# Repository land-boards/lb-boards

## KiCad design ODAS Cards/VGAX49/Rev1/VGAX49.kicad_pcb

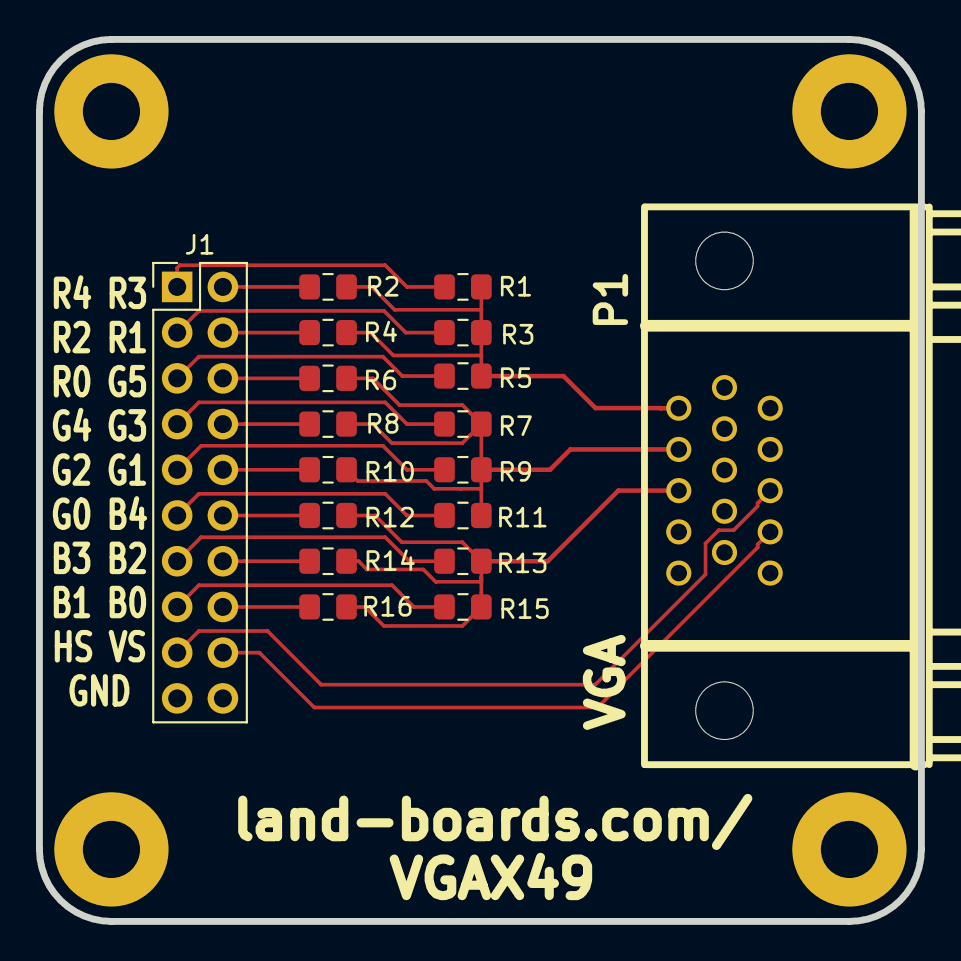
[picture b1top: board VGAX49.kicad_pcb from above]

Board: 2 copper layers, 49.0 x 49.0 mm, 22 parts (0 on the bottom side), 22 nets.

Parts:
J1: Conn_02x10_Odd_Even; PinHeader_2x10_P2.54mm_Vertical
MTG1, MTG2, MTG3, MTG4: CONN_1; MTG-4-40
P1: VGA; DB_15F-VGA-fixed
R1, R6, R12: 510; R_0805_2012Metric_Pad1.15x1.40mm_HandSolder
R2, R7, R13: 1K; R_0805_2012Metric_Pad1.15x1.40mm_HandSolder
R3, R8, R14: 2.2K; R_0805_2012Metric_Pad1.15x1.40mm_HandSolder
R4, R9, R15: 4.7K; R_0805_2012Metric_Pad1.15x1.40mm_HandSolder
R5, R10, R16: 10K; R_0805_2012Metric_Pad1.15x1.40mm_HandSolder
R11: 22K; R_0805_2012Metric_Pad1.15x1.40mm_HandSolder

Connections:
/B0: J1.16, R16.2
/B1: J1.15, R15.2
/B2: J1.14, R14.2
/B3: J1.13, R13.2
/B4: J1.12, R12.2
/G0: J1.11, R11.2
/G1: J1.10, R10.2
/G2: J1.9, R9.2
/G3: J1.8, R8.2
/G4: J1.7, R7.2
/G5: J1.6, R6.2
/HS: J1.17, P1.13
/R0: J1.5, R5.2
/R1: J1.4, R4.2
/R2: J1.3, R3.2
/R3: J1.2, R2.2
/R4: J1.1, R1.2
/VS: J1.18, P1.14
GND: J1.19, J1.20, P1.5, P1.6, P1.7, P1.8
unnamed: P1.1, R1.1, R2.1, R3.1, R4.1, R5.1
unnamed: P1.2, R6.1, R7.1, R8.1, R9.1, R10.1, R11.1
unnamed: P1.3, R12.1, R13.1, R14.1, R15.1, R16.1

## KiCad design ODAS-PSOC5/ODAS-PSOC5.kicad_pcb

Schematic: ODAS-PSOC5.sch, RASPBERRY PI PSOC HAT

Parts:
C1, C2, C3, C4, C5, C6, C9, C12, C13, C14, C15, C16: 0.1uF; C_0805_HandSoldering
C7, C10: C; C_0805_HandSoldering
C8, C11: 1uF; C_0805_HandSoldering
DS1: LED-fixed; LED_0805
F1, F2: FUSE; R_1206_HandSoldering
FID1, FID2: CONN_1; FIDUCIAL
H1: CONN_01X04; Pin_Header_Straight_1x04
H2: CONN_2; Pin_Header_Straight_2x01
H3, H4: CONN_01X03; Pin_Header_Straight_1x03
J1: DCJ0202; JACK_3.5MM
J2: USB-MICRO-B; USB_Micro-B-Wellco-SMT
MTG1, MTG2, MTG3, MTG4: CONN_1; MTG-6-32
P1: CONN_01X40; Pin_Header_Angled_2x20
P2: CONN_01X04; Pin_Header_Angled_1x04
P3: CONN_02X02; Pin_Header_Straight_2x02
P4: CONN_01X06; Pin_Header_Straight_1x06
R1: 1K; R_0805_HandSoldering
R2, R3, R4: 3.9K; R_0805_HandSoldering
R5: 120; R_0805_HandSoldering
R6, R7: 22; R_0805_HandSoldering
TEST1: COUPON; TEST_BLK-REAR
U1: 24C32; SO8E-wider
U2: CY8C5267AXI-LP051; TQFP-100_14x14mm_Pitch0.5mm
U3, U4: AP1117; SOT223
Y1: Crystal_Small; Crystal_HC49-U_Vertical

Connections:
+3.3VP: C4.1, C5.1, F1.1, H3.1, H4.1, U2.26 (VDDIO1), U2.100 (VDDIO2)
+3V3: C1.1, C15.1, C16.1, F1.2, P2.2, P4.2, R1.1, R2.2, R3.2, R4.2, U1.8 (VCC), U4.2 (VO)
+5V: C9.2, C13.1, C14.1, F2.2, U2.37 (VDDD), U2.65 (VDDA), U2.88 (VDDD), U3.2 (VO), U4.3 (VI)
+5VP: F2.1, H3.3, H4.3
/+9V: C12.1, J1.1, U3.3 (VI)
/IO_22: C2.1, H1.2, R4.1, U2.15 (~XRES)
/IO_23: H1.3, U2.21 (P1[1]/TCK/SWDCK)
/IO_24: H1.4, U2.20 (P1[0]/TMS/SWDIO)
/P5-4: R5.1, U2.31 (P5[4])
/P44: P1.34, U2.44 (P3[0])
/P45: P1.33, U2.45 (P3[1])
/P46: P1.32, U2.46 (P3[2])
/P47: P1.31, U2.47 (P3[3])
/P48: P1.30, U2.48 (P3[4])
/P49: P1.29, U2.49 (P3[5])
/P51: P1.28, U2.51 (P3[6])
/P52: P1.27, U2.52 (P3[7])
/P53: P1.26, U2.53 (I2C1_SCL/P12[0])
/P54: P1.25, U2.54 (I2C1_SDA/P12[1])
/P55: P1.24, U2.55 (P15[2])
/P56: P1.23, U2.56 (P15[3])
/P67: P1.22, U2.67 (P12[2])
/P68: P1.21, U2.68 (P12[3])
/P69: P1.20, U2.69 (P4[0])
/P70: P1.19, U2.70 (P4[1])
/P71: P1.18, U2.71 (P0[0])
/P72: P1.17, U2.72 (P0[1])
/P73: P1.16, U2.73 (P0[2])
/P74: P1.15, U2.74 (P0[3])
/P76: P1.14, U2.76 (P0[4])
/P77: P1.13, U2.77 (P0[5])
/P78: P1.12, U2.78 (P0[6])
/P79: P1.11, U2.79 (P0[7])
/P80: P1.10, U2.80 (P4[2])
/P81: P1.9, U2.81 (P4[3])
/P82: P1.8, U2.82 (P4[4])
/P83: P1.7, U2.83 (P4[5])
/P84: P1.6, U2.84 (P4[6])
/P85: P1.5, U2.85 (P4[7])
/SCL: P2.4, P3.4, U1.6 (SCL), U2.4 (I2C0_SCL/P12[4])
/SDA: P2.3, P3.2, U1.5 (SDA), U2.5 (I2C2_SDA/P12[5])
/SPICE0: P4.3, U2.6 (P6[4])
/SPIMISO: P4.5, U2.8 (P6[6])
/SPIMOSI: P4.6, U2.9 (P6[7])
/SPISCK: P4.4, U2.7 (P6[5])
/USB-DM: J2.2 (D-), R6.1
/USB-DP: J2.3 (D+), R7.1
/VZ0: C3.1, H4.2, P1.3, P1.4, U2.75 (VDDIO0)
/VZ3: C6.1, H3.2, P1.35, P1.36, U2.50 (VDDIO3)
/WR: H2.1, R1.2, U1.7 (~WP)
GND: C1.2, C2.2, C3.2, C4.2, C5.2, C6.2, C7.1, C8.1, C9.1, C10.1, C11.1, C12.2, C13.2, C14.2, C15.2, C16.2, DS1.1, H1.1, H2.2 (PM), J1.2, J1.3, J2.5 (GND), P1.1, P1.2, P1.37, P1.38, P2.1, P4.1, U1.1 (A0), U1.2 (A1), U1.3 (A2), U1.4 (GND), U2.10 (VSSB), U2.12 (VBOOST), U2.13 (VBAT), U2.14 (VSSD), U2.38 (VSSD), U2.64 (VSSA), U2.66 (VSSD), U2.87 (VSSD), U3.1 (GND/ADJ), U4.1 (GND/ADJ)
unnamed: C7.2, U2.43 (P15[1]), Y1.1
unnamed: C8.2, U2.39 (VCCD), U2.86 (VCCD)
unnamed: C10.2, U2.42 (P15[0]), Y1.2
unnamed: C11.2, U2.63 (VCCA)
unnamed: DS1.2, R5.2
unnamed: P3.1, R2.1
unnamed: P3.3, R3.1
unnamed: R6.2, U2.36 (DM/P15[7])
unnamed: R7.2, U2.35 (DP/P15[6])

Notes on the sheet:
WRITE ENABLE

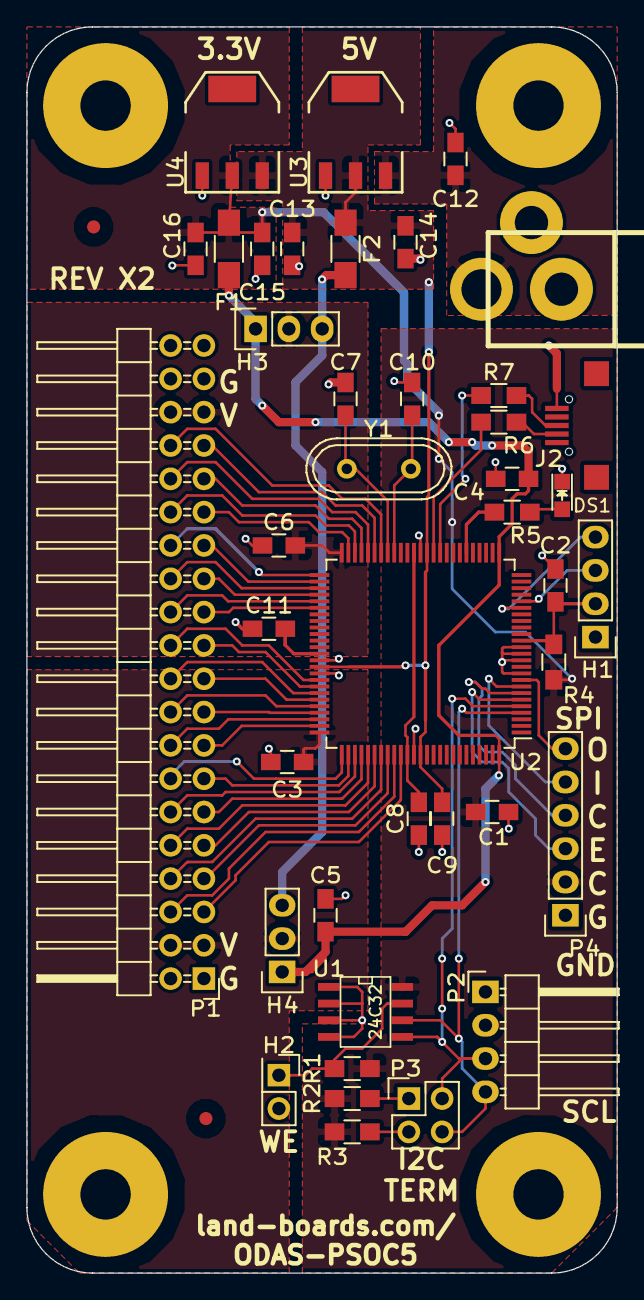
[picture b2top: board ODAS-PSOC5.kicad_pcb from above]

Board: 2 copper layers, 45.0 x 95.0 mm, 48 parts (1 on the bottom side), 60 nets.

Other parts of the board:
TEST: COUPON; REV_BLOCK

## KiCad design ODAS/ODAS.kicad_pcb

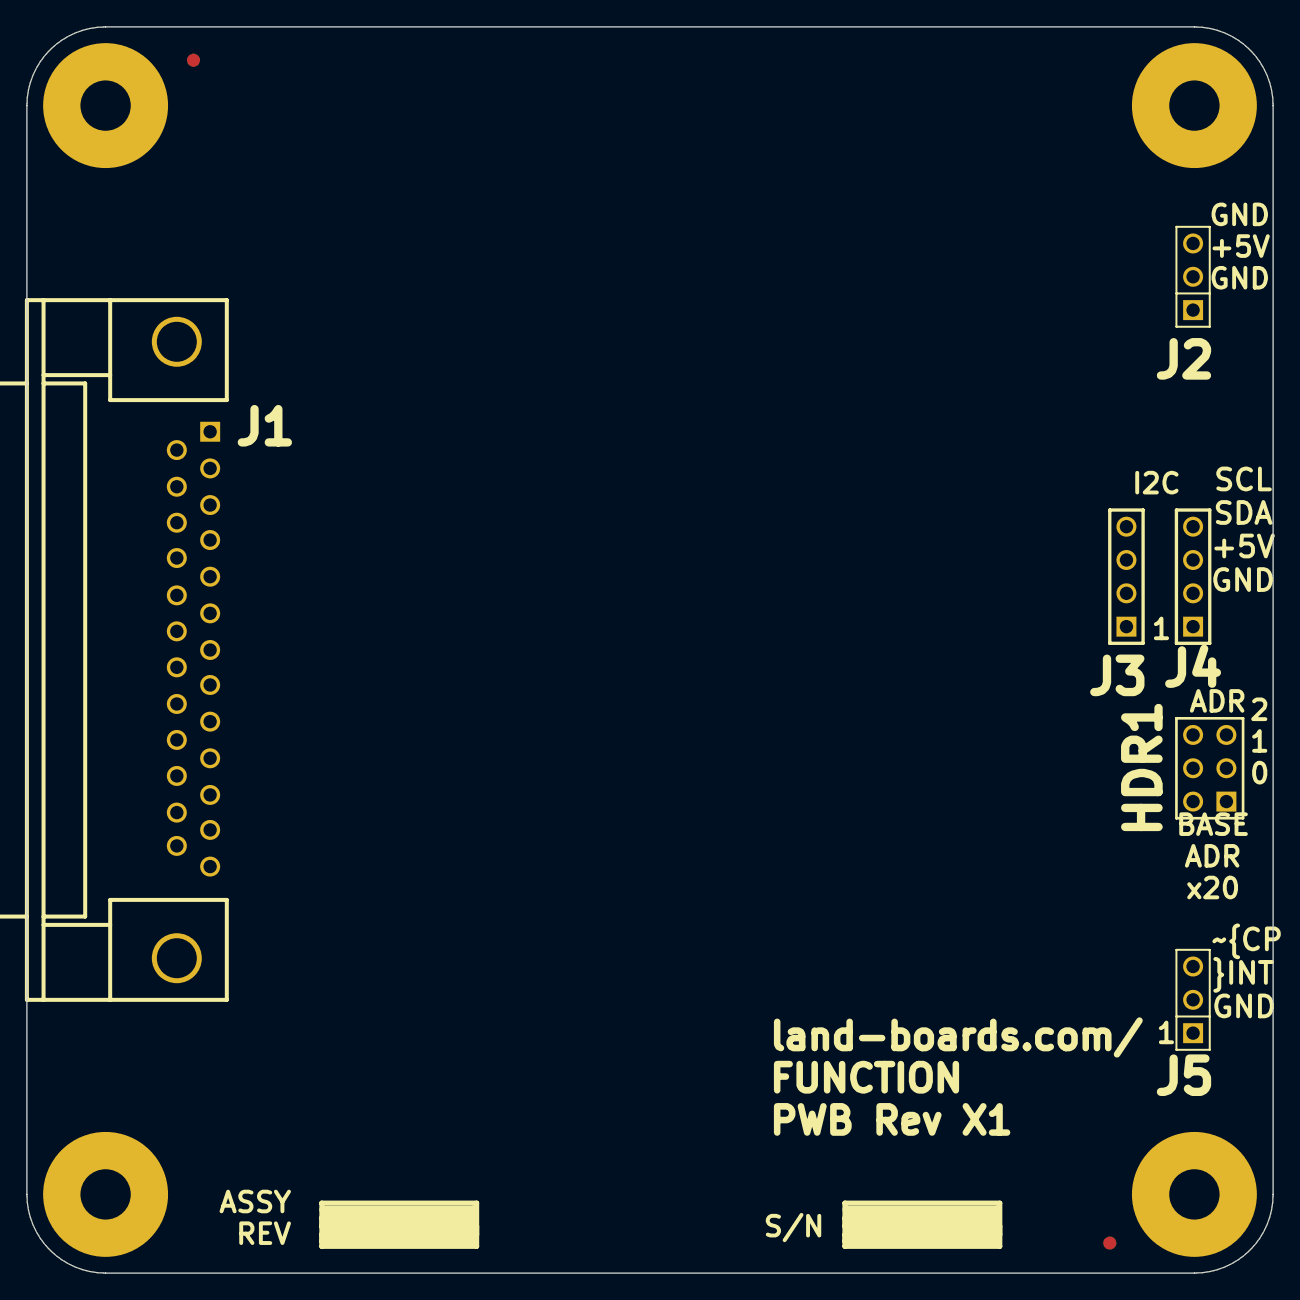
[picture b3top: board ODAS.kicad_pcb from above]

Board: 2 copper layers, 95.0 x 95.0 mm, 14 parts (0 on the bottom side), 4 nets.

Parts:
FID1, FID2: ADAFRUIT_FIDUCIAL; FIDUCIAL
HDR1: CONN_3X2; pin_array_3x2
J1: DB25; DB25MC
J2, J5: CONN_3; PIN_ARRAY_3X1
J3, J4: CONN_4; PIN_ARRAY_4x1
MTG1, MTG2, MTG3, MTG4: MTG_HOLE; MTG-6-32
ST1: CONN_1; REV_BLOCK
ST2: REV-HIST; REV_BLOCK

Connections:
/GND: HDR1.1, HDR1.3, HDR1.5, J2.1, J2.3, J3.1, J4.1, J5.1, J5.3
/SCK: J3.4, J4.4
/SDA: J3.3, J4.3
/VCC: J2.2, J3.2, J4.2

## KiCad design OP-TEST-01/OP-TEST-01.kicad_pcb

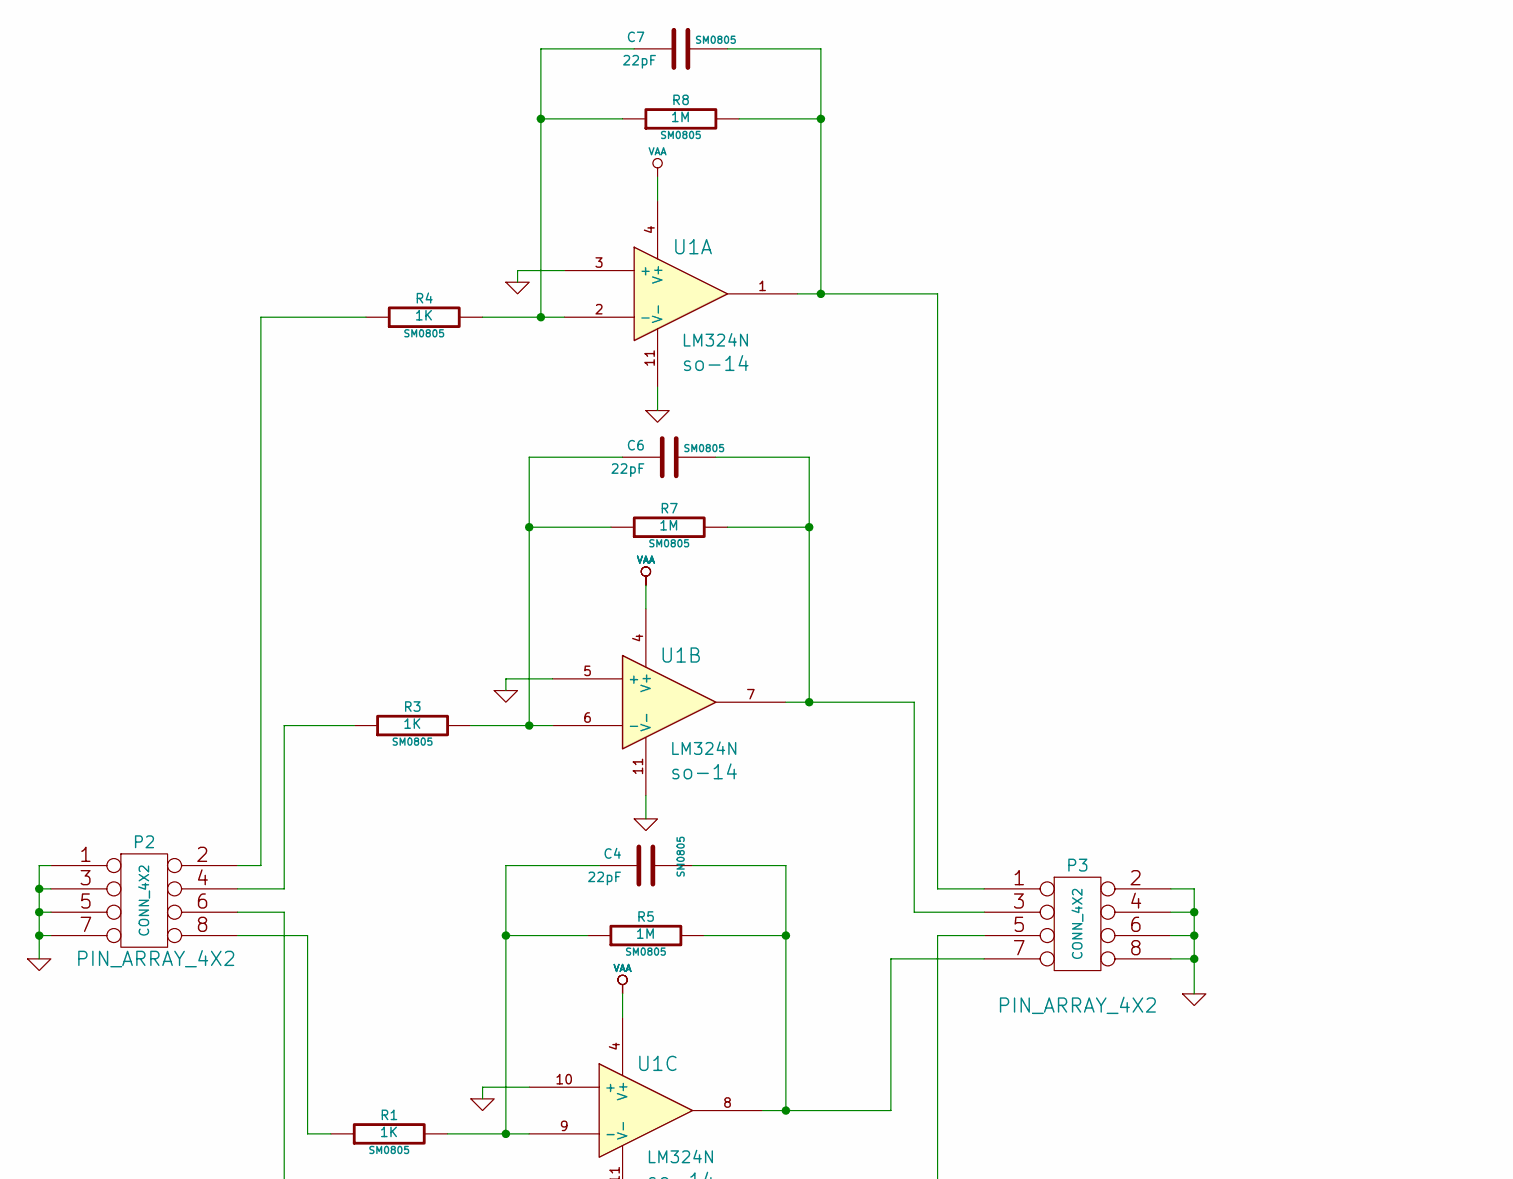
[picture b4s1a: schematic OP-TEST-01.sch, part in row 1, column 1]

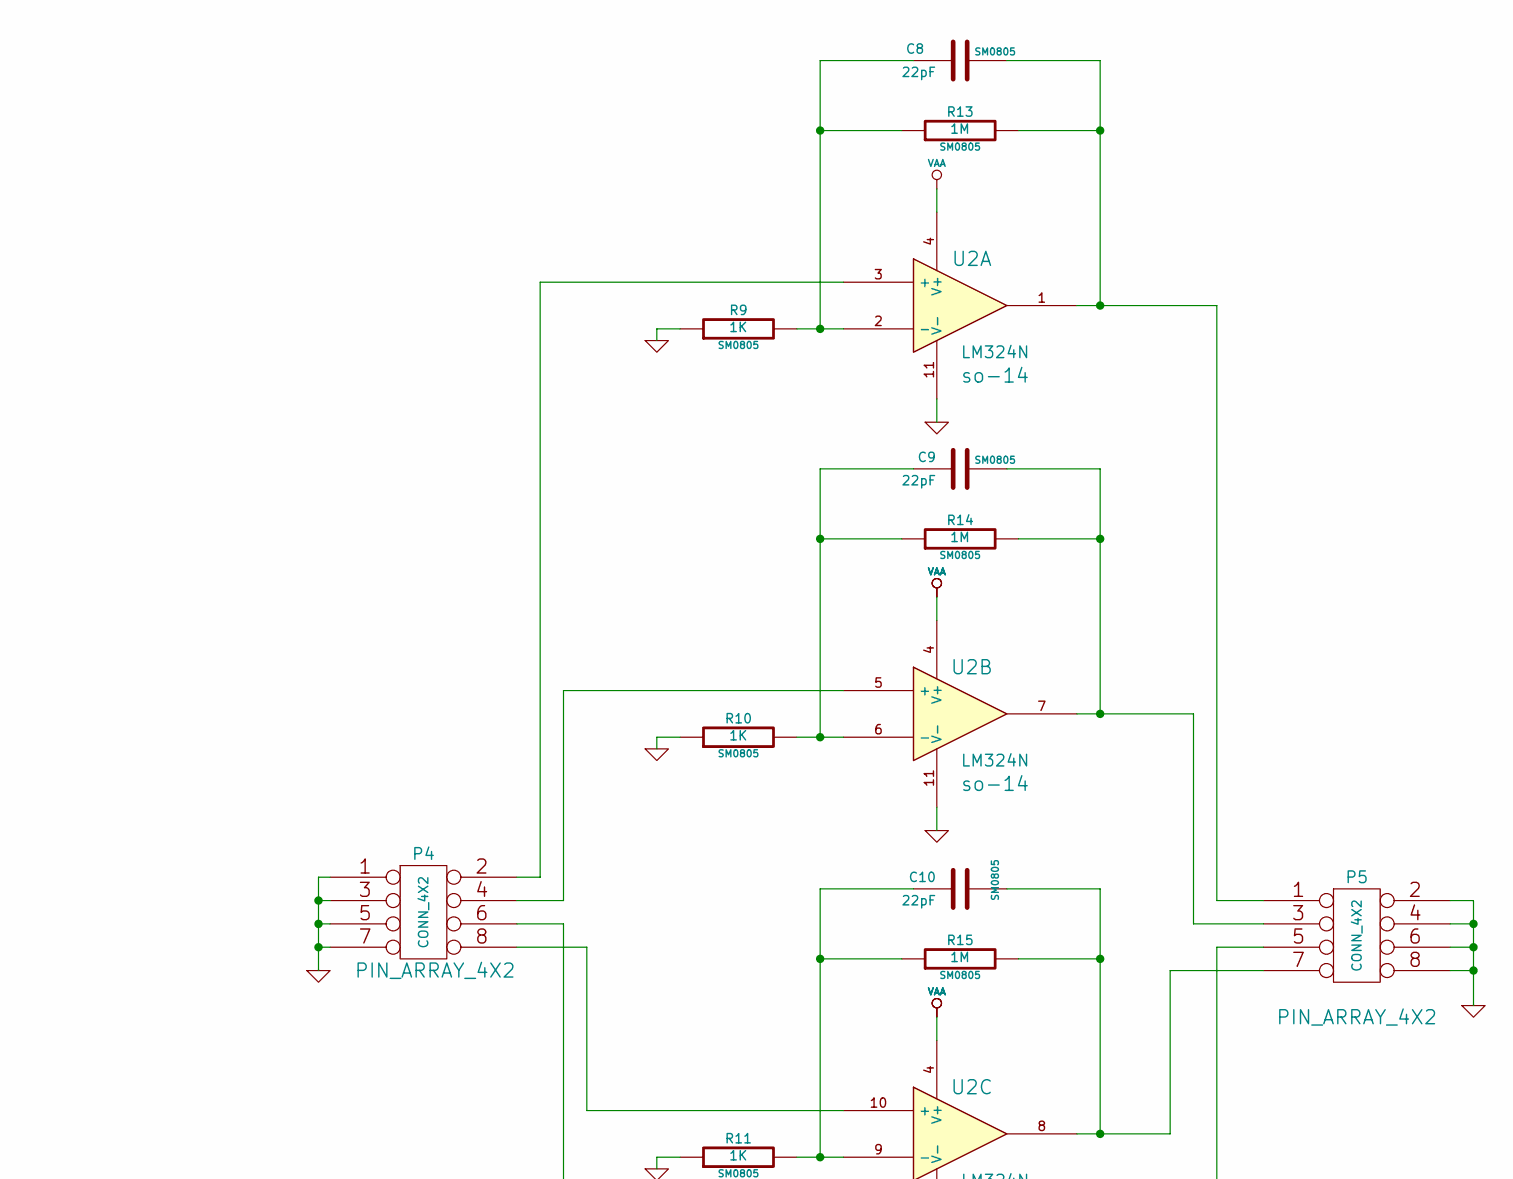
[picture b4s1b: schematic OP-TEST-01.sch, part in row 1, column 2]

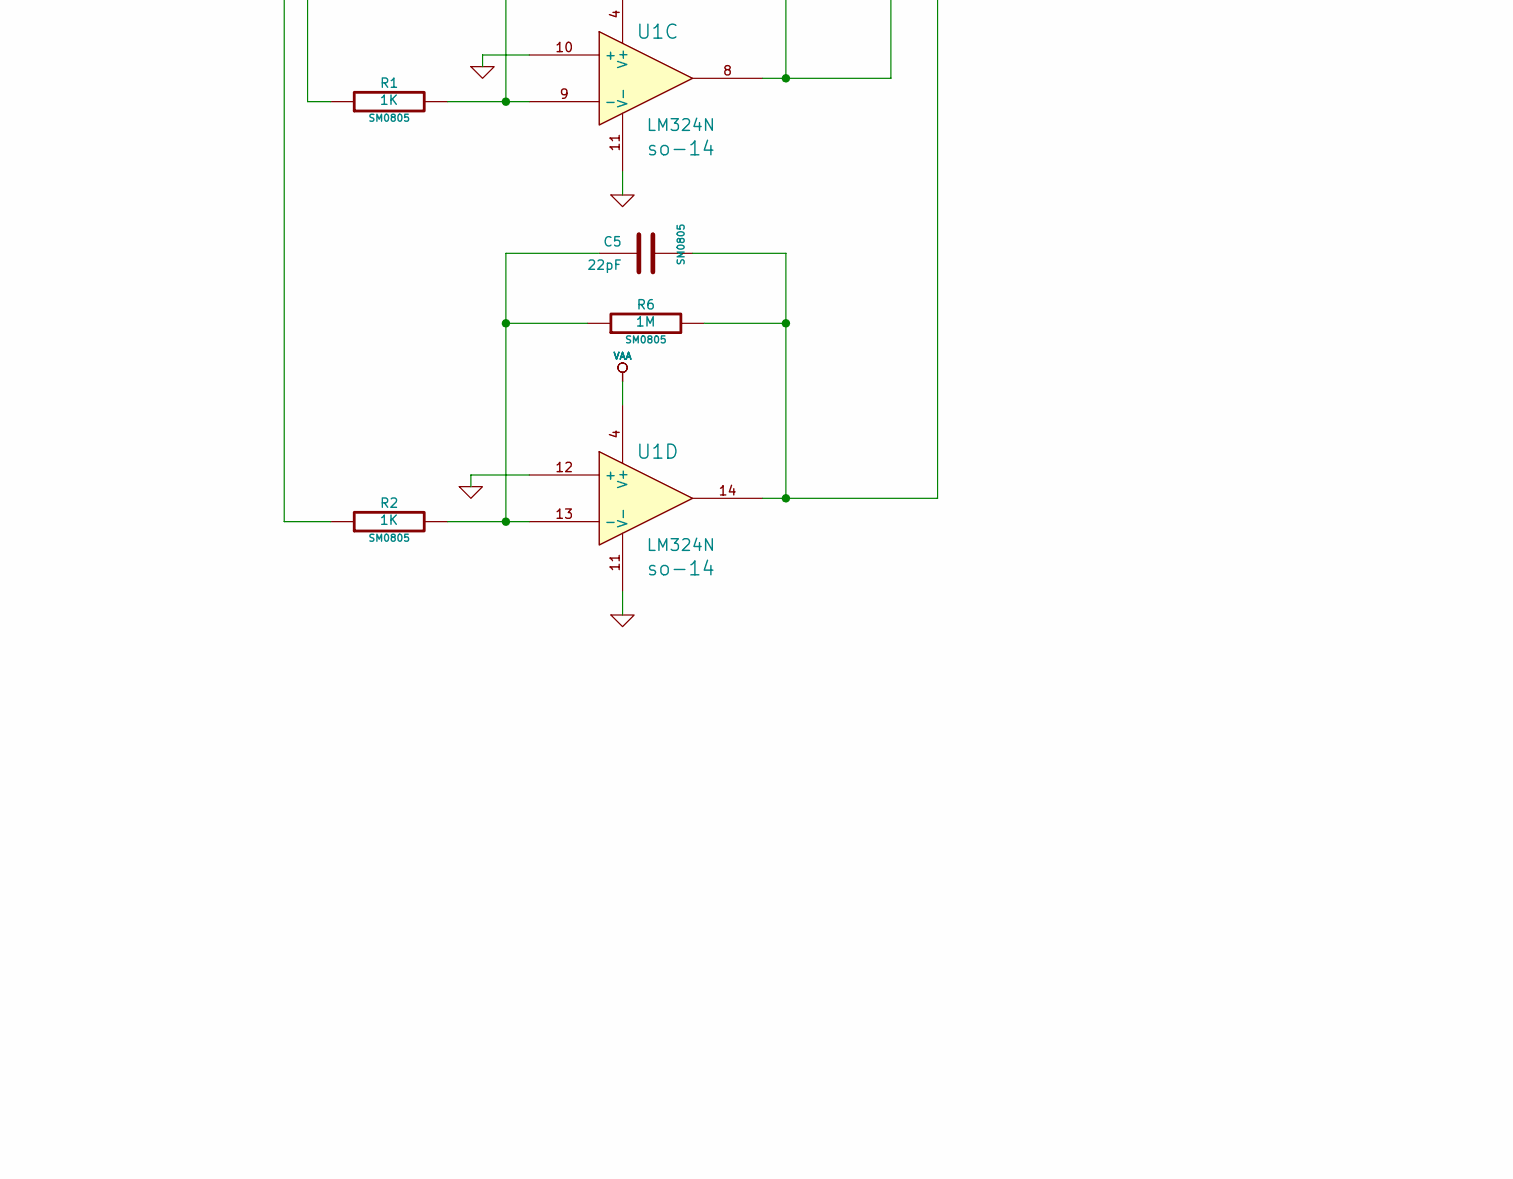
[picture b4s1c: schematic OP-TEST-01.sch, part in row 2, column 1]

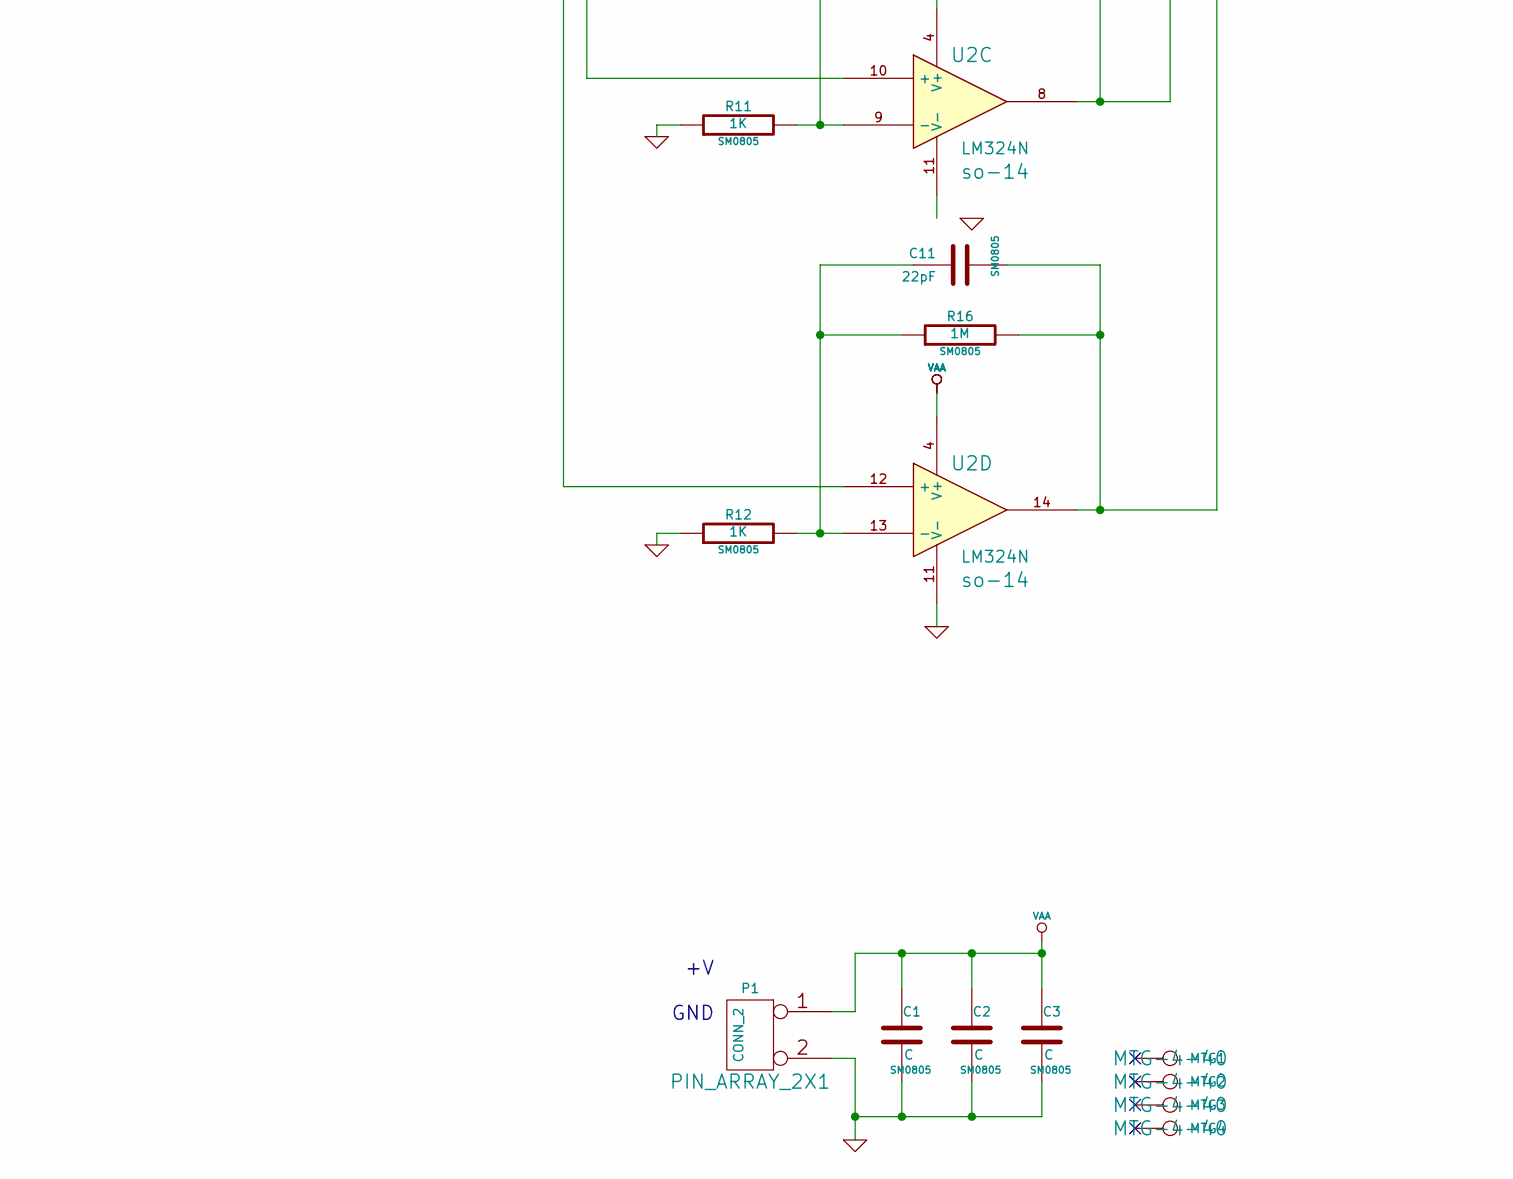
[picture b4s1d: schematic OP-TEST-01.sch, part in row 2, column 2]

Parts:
C1, C2, C3: C; SM0805
C4, C5, C6, C7, C8, C9, C10, C11: 22pF; SM0805
MTG1, MTG2, MTG3, MTG4: CONN_1; MTG-4-40
P1: CONN_2; PIN_ARRAY_2X1
P2, P3, P4, P5: CONN_4X2; PIN_ARRAY_4X2
R1, R2, R3, R4, R9, R10, R11, R12: 1K; SM0805
R5, R6, R7, R8, R13, R14, R15, R16: 1M; SM0805
U1, U2: LM324N; so-14

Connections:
GND: C1.2, C2.2, C3.2, P1.2 (PM), P2.1, P2.3, P2.5, P2.7, P3.2, P3.4, P3.6, P3.8, P4.1, P4.3, P4.5, P4.7, P5.2, P5.4, P5.6, P5.8, R9.1, R10.1, R11.1, R12.1, U1.3 (+), U1.5 (+), U1.10 (+), U1.11 (V-), U1.12 (+), U2.11 (V-)
unnamed: C8.2, P5.1, R13.2, U2.1
unnamed: C8.1, R9.2, R13.1, U2.2 (-)
unnamed: C10.1, R11.2, R15.1, U2.9 (-)
unnamed: C10.2, P5.7, R15.2, U2.8
unnamed: C9.2, P5.3, R14.2, U2.7
unnamed: C9.1, R10.2, R14.1, U2.6 (-)
unnamed: P4.4, U2.5 (+)
unnamed: P4.8, U2.10 (+)
unnamed: P4.6, U2.12 (+)
unnamed: P4.2, U2.3 (+)
unnamed: C11.2, P5.5, R16.2, U2.14
unnamed: C11.1, R12.2, R16.1, U2.13 (-)
unnamed: P2.2, R4.1
unnamed: C7.2, P3.1, R8.2, U1.1
unnamed: P2.4, R3.1
unnamed: C5.2, P3.5, R6.2, U1.14
unnamed: P2.6, R2.1
unnamed: P2.8, R1.1
unnamed: C6.2, P3.3, R7.2, U1.7
unnamed: C6.1, R3.2, R7.1, U1.6 (-)
unnamed: C4.1, R1.2, R5.1, U1.9 (-)
unnamed: C7.1, R4.2, R8.1, U1.2 (-)
unnamed: C5.1, R2.2, R6.1, U1.13 (-)
unnamed: C4.2, P3.7, R5.2, U1.8
VAA: C1.1, C2.1, C3.1, P1.1, U1.4 (V+), U2.4 (V+)

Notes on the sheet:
+V GND

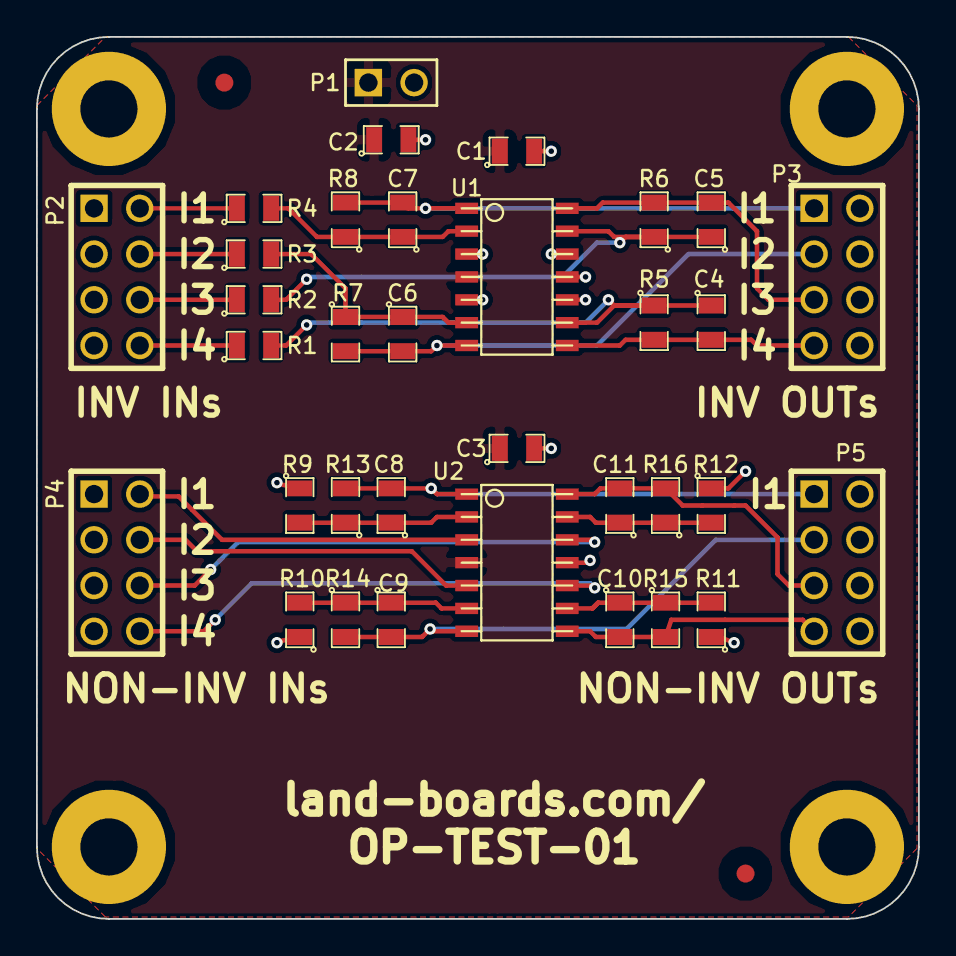
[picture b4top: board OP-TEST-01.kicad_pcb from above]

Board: 2 copper layers, 49.0 x 49.0 mm, 40 parts (0 on the bottom side), 26 nets.

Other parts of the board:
FIDUCIAL: VAL**; FIDUCIAL
FIDUCIAL#2: VAL**; FIDUCIAL

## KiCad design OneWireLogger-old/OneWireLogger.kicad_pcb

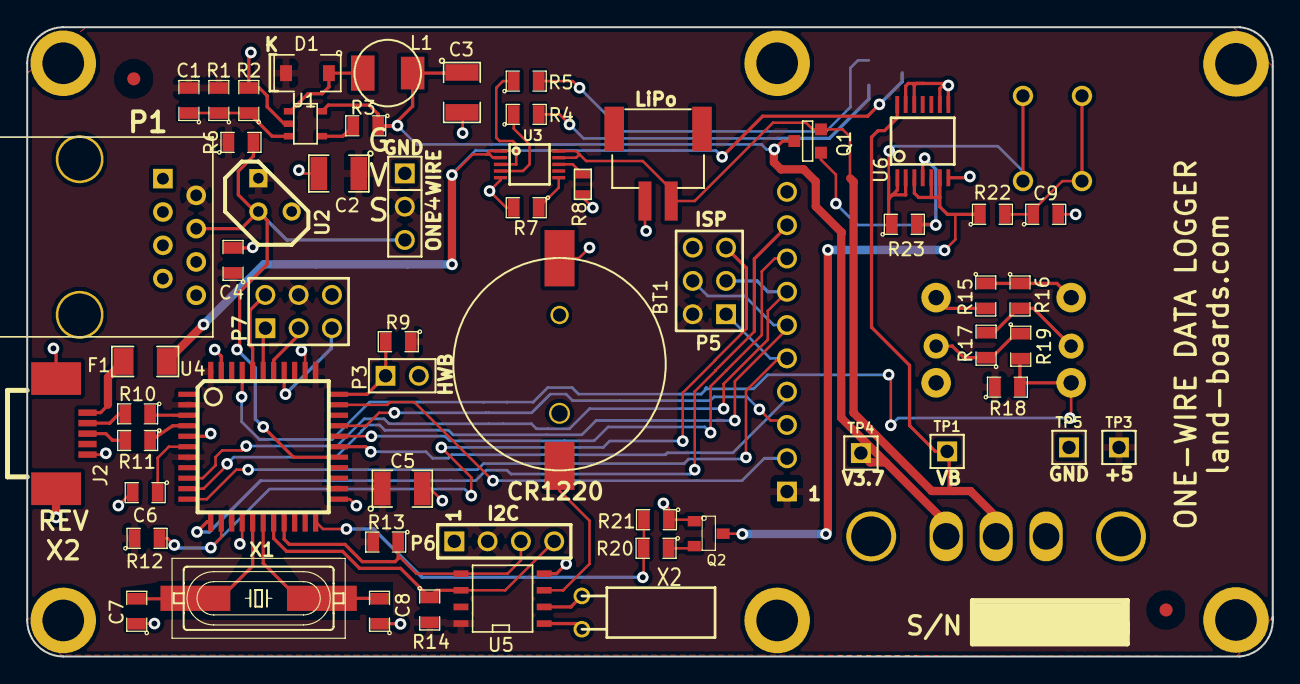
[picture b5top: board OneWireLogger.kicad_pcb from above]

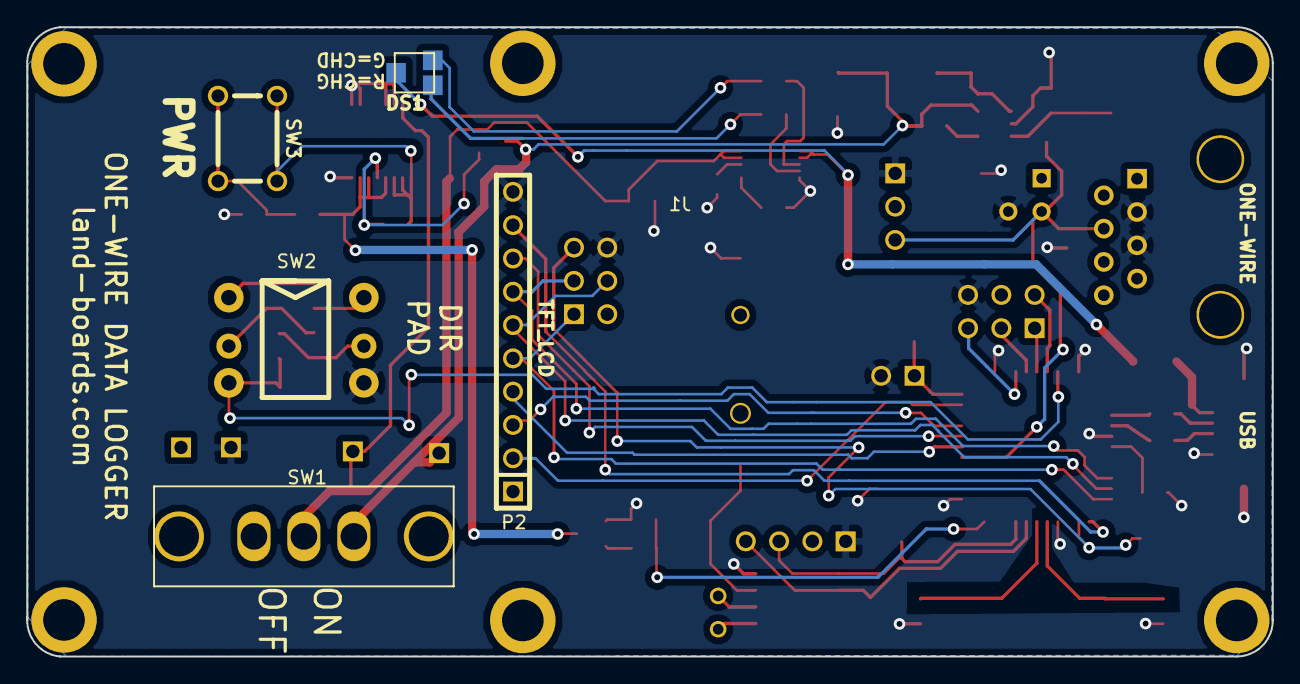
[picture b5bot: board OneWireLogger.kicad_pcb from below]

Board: 2 copper layers, 95.0 x 48.0 mm, 72 parts (5 on the bottom side), 53 nets.

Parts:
BT1: BATTERY; CR1220_CASE
C1: 680pF; SM0805
C2, C3: 4.7uF; SM1210
C4, C9: 0.1uF; SM0805
C5: 10uF; SM1210
C6: 1uF; SM0805
C7, C8: 18pF; SM0805
D1: MBR0520LT1G; SOD-123
DS1: LED2C_CA; SOT23_LED2C
F1: FUSE; SM1206
FID1, FID2: CONN_1; FIDUCIAL
J1: JST_2; JST-2-SMT
J2: USB-B; USB-B-MINI
L1: 10uH; IND-3MM
MTG1, MTG2, MTG3, MTG4, MTG5, MTG6: CONN_1; MTG-4-40-SMALL
P1: CNT-RJ45-8; RJ45_8-TH
P2: TFT_LCD; PIN_ARRAY-10X1
P3: CONN_2; PIN_ARRAY_2X1
P4: CONN_3; PIN_ARRAY_3X1
P5, P7: CONN_3X2; pin_array_3x2
P6: CONN_4; PIN_ARRAY_4x1
Q1: DMG3415U-7; SOT23GDS
Q2: 2N3904; SOT23
R1: 3.09K; SM0805
R2, R16, R20: 1K; SM0805
R3: 1M; SM0805
R4, R5: 470; SM0805
R6: 4.7K; SM0805
R7: 2.2K; SM0805
R8: NTC-10K; SM0603
R9, R12, R13, R14, R21: 10K; SM0805
R10, R11: 22; SM0805
R15: 3.3K; SM0805
R17: 560; SM0805
R18: 1.8K; SM0805
R19: 330; SM0805
R22, R23: 100K; SM0805
REV_BLOCK1: REV_BLOCK
SW1: SW-SPDT; SW-SPDT-SLIDE
SW2: SW5WAY
SW3: SW_PUSH_OMRON; SW-PB-6MM
TP1, TP3, TP4, TP5: TST; PIN_ARRAY_1
U1: LMR62014; SOT23-5
U2: DS18S20+; TO92-123
U3: MCP73833; MSOP10-0.5
U4: ATMEGA32U4-AU; TQFP44
U5: DS1307; SO8N
U6: MC14093; TSSOP14
X1: CRYSTAL; crystal-HC49UP
X2: 32.768KHz; QMONTRE

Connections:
+5V: C1.2, C2.1, C4.1, C5.1, D1.2, P1.2, P2.1, P4.2, P5.2, P6.2, P7.4, R1.2, R6.1, R9.1, R12.1, R13.2, R14.2, R18.1, TP3.1, U2.3, U4.2, U4.7, U4.14, U4.24, U4.34, U4.44, U5.8
/5-Way Switch/SW5WAY: R18.2, R19.2, SW2.3, U4.41
/5V Power Supply/3.7V: C3.1, L1.1, Q1.D, R3.1, SW1.1, TP4.1, U1.5
/LiPo Battery Charger/VB-3.7: J1.2, Q1.S, SW1.2, TP1.1, U3.9, U3.10, U6.14
/Microprocessor/ADC1: P7.2, U4.40
/Microprocessor/ADC4: P7.1, U4.39
/Microprocessor/ADC5: P7.3, U4.38
/Microprocessor/ADC6: P7.5, U4.37
/Microprocessor/BKLT: P2.2, U4.32
/Microprocessor/BUSBP: R11.1, U4.4
/Microprocessor/BUSPM: R10.1, U4.3
/Microprocessor/LCDCS: P2.8, U4.29
/Microprocessor/LCDRS: P2.4, U4.28
/Microprocessor/LCDRST: P2.3, U4.30
/Microprocessor/MISO: P2.5, P5.1, U4.11
/Microprocessor/MOSI: P2.6, P5.4, U4.10
/Microprocessor/ONE-WIRE: P1.4, P4.3, R6.2, U2.2, U4.27
/Microprocessor/PWR-OFF: R20.2, R21.2, U4.22
/Microprocessor/RST: P5.5, R12.2, U4.13
/Microprocessor/SCK: P2.7, P5.3, U4.9
/Microprocessor/SCLK: P6.4, R14.1, U4.18, U5.6
/Microprocessor/SDA: P6.3, R13.1, U4.19, U5.5
/Microprocessor/SDCS: P2.9, U4.12
/Microprocessor/USB5V: F1.2, J2.1
/Microprocessor/USB-DM: J2.2, R10.2
/Microprocessor/USB-DP: J2.3, R11.2
/Microprocessor/V5USB: DS1.ANOD, F1.1, U3.1, U3.2
/Microprocessor/~HWB: P3.1, R9.2, U4.33
/PowerSwitch/GATE: Q1.G, R23.2, U6.4
GND: BT1.2, C2.2, C3.2, C4.2, C5.2, C6.2, C7.1, C8.1, C9.2, J1.1, J2.4, J2.G1, J2.G2, P1.3, P1.5, P2.10, P3.2, P4.1, P5.6, P6.1, P7.6, Q2.1, R2.2, R7.2, R8.2, R21.1, SW2.4, TP5.1, U1.2, U2.1, U3.5, U4.5, U4.15, U4.23, U4.35, U4.43, U5.4, U6.7, U6.8, U6.9, U6.12, U6.13
unnamed: R7.1, U3.6
unnamed: R4.1, U3.4
unnamed: R8.1, U3.8
unnamed: DS1.RED, R5.2
unnamed: DS1.GRN, R4.2
unnamed: R5.1, U3.3
unnamed: C1.1, R1.1, R2.1, U1.3
unnamed: D1.1, L1.2, U1.1
unnamed: R3.2, U1.4
unnamed: BT1.1, U5.3
unnamed: C8.2, U4.17, X1.2
unnamed: U5.1, X2.1
unnamed: U5.2, X2.2
unnamed: C7.2, U4.16, X1.1
unnamed: C6.1, U4.6
unnamed: R17.1, R19.1, SW2.5
unnamed: R15.2, SW2.6
unnamed: R16.2, R17.2, SW2.2
unnamed: R15.1, R16.1, SW2.1
unnamed: Q2.2, R20.1
unnamed: C9.1, R22.2, SW3.1, SW3.2
unnamed: R23.1, SW3.3, SW3.4, U6.1, U6.2
unnamed: Q2.3, R22.1, U6.3, U6.5, U6.6
